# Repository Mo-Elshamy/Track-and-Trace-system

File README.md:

# Track-and-Trace-system 
Used on a medicine production line 
This project is a base module that can be customized for specific purposes.

Youtube link : https://youtu.be/wrTnvzPaxEU

In this project, my role was to establish communication with a microcontroller via a Python app, with the microcontroller responding to any action such as rejection or approval in the production line.

## Python code:

This code is a demonstration of the app code that is responsible for of processing the image from the camera. When the object is detected by the microcontroller, the first section decodes the QR code, and the second section extracts the text from a frame saved as an image.The text from the QR code is then compared to the text from the captured image to make a decision.
The code communicates with the serial library by specifying the port and the baud rate.

## Microconntroller code:

This code is responsible for the app code's actions and also sends a string to the app that acts as a trigger to notify the app code when an object is detected using an IR sensor.

## Hardware circuit:

This circuit is designed to have:
* 4 output relay
* 2 IR sesonrs
* RGBA 12v output connection
* 12v, 5v and GND output
* Input power 24V

## System schematic:

## Pico pinout connection:

## layout design:

## Crcuit:

## Test:

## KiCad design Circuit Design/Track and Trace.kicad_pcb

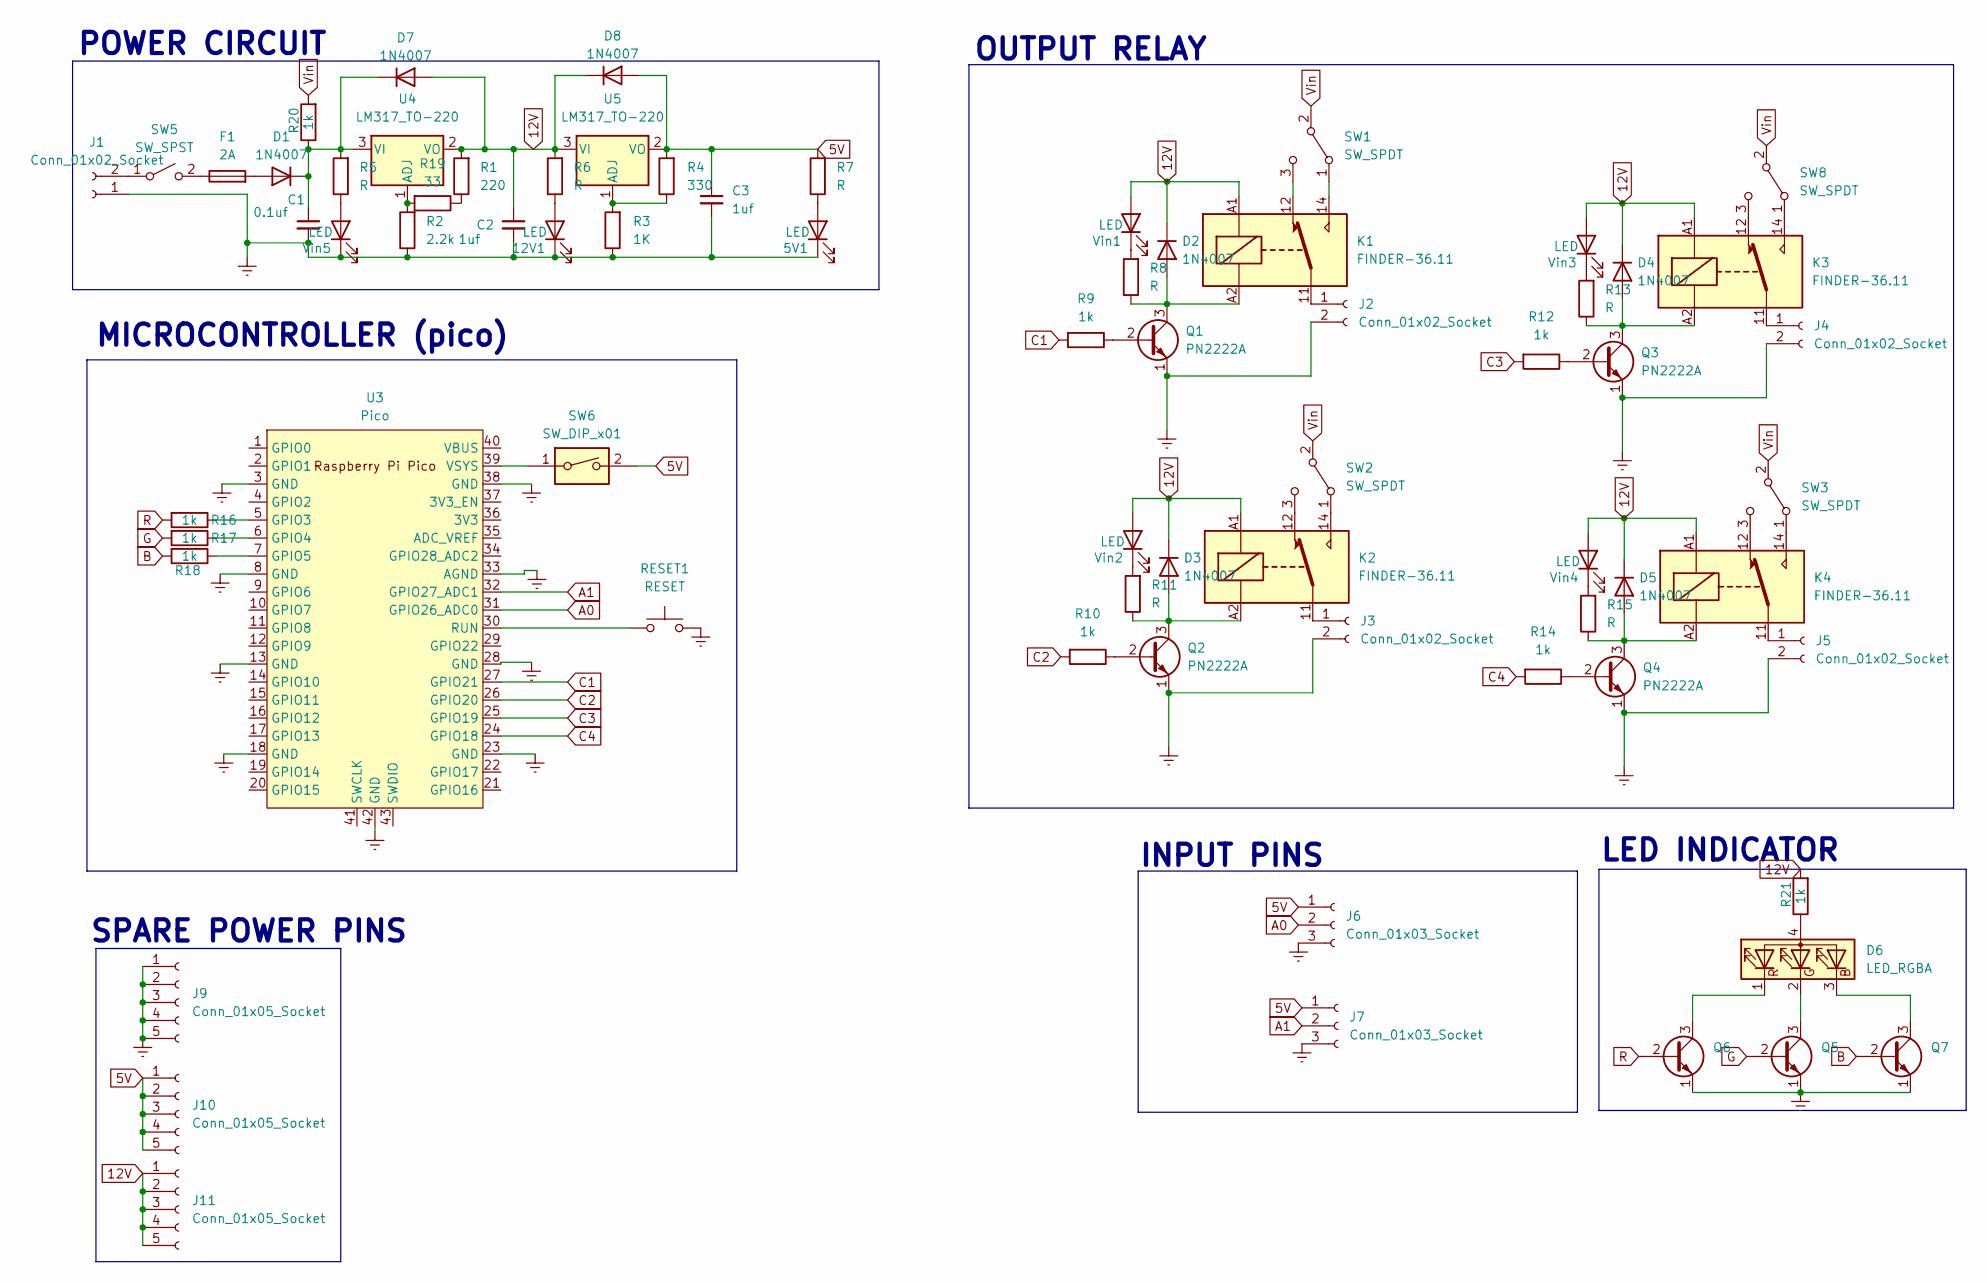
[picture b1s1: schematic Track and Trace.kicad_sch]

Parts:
5V1, 12V1: LED; LED_D3.0mm
C1: 0.1uf; CP_Radial_D4.0mm_P2.00mm
C2, C3: 1uf; CP_Radial_D4.0mm_P2.00mm
D1, D2, D3, D4, D5, D7, D8: 1N4007; D_DO-41_SOD81_P10.16mm_Horizontal
D6: LED_RGBA; JST_EH_B4B-EH-A_1x04_P2.50mm_Vertical
F1: 2A; Fuseholder_Littelfuse_100_series_5x20mm
J1, J2, J3, J4, J5: Conn_01x02_Socket; TerminalBlock_bornier-2_P5.08mm
J6, J7: Conn_01x03_Socket; JST_EH_B3B-EH-A_1x03_P2.50mm_Vertical
J9, J10, J11: Conn_01x05_Socket; TerminalBlock_bornier-5_P5.08mm
K1, K2, K3, K4: FINDER-36.11; Relay_SPDT_Finder_36.11
Q1, Q2, Q3, Q4, Q5, Q6, Q7: PN2222A; TO-92_Inline
R1: 220; R_Axial_DIN0207_L6.3mm_D2.5mm_P10.16mm_Horizontal
R2: 2.2k; R_Axial_DIN0207_L6.3mm_D2.5mm_P10.16mm_Horizontal
R3: 1K; R_Axial_DIN0207_L6.3mm_D2.5mm_P10.16mm_Horizontal
R4: 330; R_Axial_DIN0207_L6.3mm_D2.5mm_P10.16mm_Horizontal
R5, R6, R7, R8, R11, R13, R15: R; R_Axial_DIN0207_L6.3mm_D2.5mm_P10.16mm_Horizontal
R9, R10, R12, R14, R16, R17, R18, R20, R21: 1k; R_Axial_DIN0207_L6.3mm_D2.5mm_P10.16mm_Horizontal
R19: 33; R_Axial_DIN0207_L6.3mm_D2.5mm_P10.16mm_Horizontal
RESET1: RESET; SW_PUSH_6mm_H5mm
SW1, SW2, SW3, SW8: SW_SPDT; PinHeader_1x03_P2.54mm_Vertical
SW5: SW_SPST; TerminalBlock_bornier-2_P5.08mm
SW6: SW_DIP_x01; SW_DIP_SPSTx01_Piano_10.8x4.1mm_W7.62mm_P2.54mm
U3: Pico; RPi_Pico_SMD_TH
U4, U5: LM317_TO-220; TO-220-3_Vertical
Vin1, Vin2, Vin3, Vin4, Vin5: LED; LED_D3.0mm

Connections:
5V: C3.1, D8.2 (A), J6.1, J7.1, J10.1, J10.2, J10.3, J10.4, J10.5, R4.2, R7.2, SW6.2, U5.2 (VO)
12V: C2.1, D2.1 (K), D3.1 (K), D4.1 (K), D5.1 (K), D7.2 (A), D8.1 (K), J11.1, J11.2, J11.3, J11.4, J11.5, K1.A1, K2.A1, K3.A1, K4.A1, R1.2, R6.2, R21.2, U4.2 (VO), U5.3 (VI), Vin1.2 (A), Vin2.2 (A), Vin3.2 (A), Vin4.2 (A)
A0: J6.2, U3.31 (GPIO26_ADC0)
A1: J7.2, U3.32 (GPIO27_ADC1)
B: Q7.2 (B), R18.2
C1: R9.2, U3.27 (GPIO21)
C2: R10.2, U3.26 (GPIO20)
C3: R12.2, U3.25 (GPIO19)
C4: R14.2, U3.24 (GPIO18)
Earth: 5V1.1 (K), 12V1.1 (K), C1.2, C2.2, C3.2, J1.1, J2.2, J3.2, J4.2, J5.2, J6.3, J7.3, J9.1, J9.2, J9.3, J9.4, J9.5, Q1.1 (E), Q2.1 (E), Q3.1 (E), Q4.1 (E), Q5.1 (E), Q6.1 (E), Q7.1 (E), R2.1, R3.1, RESET1.2, U3.3 (GND), U3.8 (GND), U3.13 (GND), U3.18 (GND), U3.23 (GND), U3.28 (GND), U3.33 (AGND), U3.38 (GND), U3.42 (GND), Vin5.1 (K)
G: Q5.2 (B), R17.2
unnamed: 5V1.2 (A), R7.1
unnamed: 12V1.2 (A), R6.1
unnamed: D1.2 (A), F1.2
unnamed: C1.1, D1.1 (K), D7.1 (K), R5.2, R20.1, U4.3 (VI)
unnamed: D2.2 (A), K1.A2, Q1.3 (C), R8.1
unnamed: D3.2 (A), K2.A2, Q2.3 (C), R11.1
unnamed: D4.2 (A), K3.A2, Q3.3 (C), R13.1
unnamed: D5.2 (A), K4.A2, Q4.3 (C), R15.1
unnamed: D6.4 (A), R21.1
unnamed: D6.3 (BK), Q7.3 (C)
unnamed: D6.2 (GK), Q5.3 (C)
unnamed: D6.1 (RK), Q6.3 (C)
unnamed: J1.2, SW5.1 (A)
unnamed: J2.1, K1.11
unnamed: J3.1, K2.11
unnamed: J4.1, K3.11
unnamed: J5.1, K4.11
unnamed: Q1.2 (B), R9.1
unnamed: Q2.2 (B), R10.1
unnamed: Q3.2 (B), R12.1
unnamed: Q4.2 (B), R14.1
unnamed: R1.1, R19.1
unnamed: K1.14, SW1.1 (A)
unnamed: K1.12, SW1.3 (C)
unnamed: K2.14, SW2.1 (A)
unnamed: K2.12, SW2.3 (C)
unnamed: K4.14, SW3.1 (A)
unnamed: K4.12, SW3.3 (C)
unnamed: F1.1, SW5.2 (B)
unnamed: K3.14, SW8.1 (A)
unnamed: K3.12, SW8.3 (C)
unnamed: R16.1, U3.5 (GPIO3)
unnamed: R17.1, U3.6 (GPIO4)
unnamed: R18.1, U3.7 (GPIO5)
unnamed: RESET1.1, U3.30 (RUN)
unnamed: SW6.1, U3.39 (VSYS)
unnamed: R2.2, R19.2, U4.1 (ADJ)
unnamed: R3.2, R4.1, U5.1 (ADJ)
unnamed: R8.2, Vin1.1 (K)
unnamed: R11.2, Vin2.1 (K)
unnamed: R13.2, Vin3.1 (K)
unnamed: R15.2, Vin4.1 (K)
unnamed: R5.1, Vin5.2 (A)
R: Q6.2 (B), R16.2
Vin: R20.2, SW1.2 (B), SW2.2 (B), SW3.2 (B), SW8.2 (B)

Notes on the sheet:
SPARE POWER PINS
LED INDICATOR
MICROCONTROLLER (pico)
OUTPUT RELAY
INPUT PINS
POWER CIRCUIT

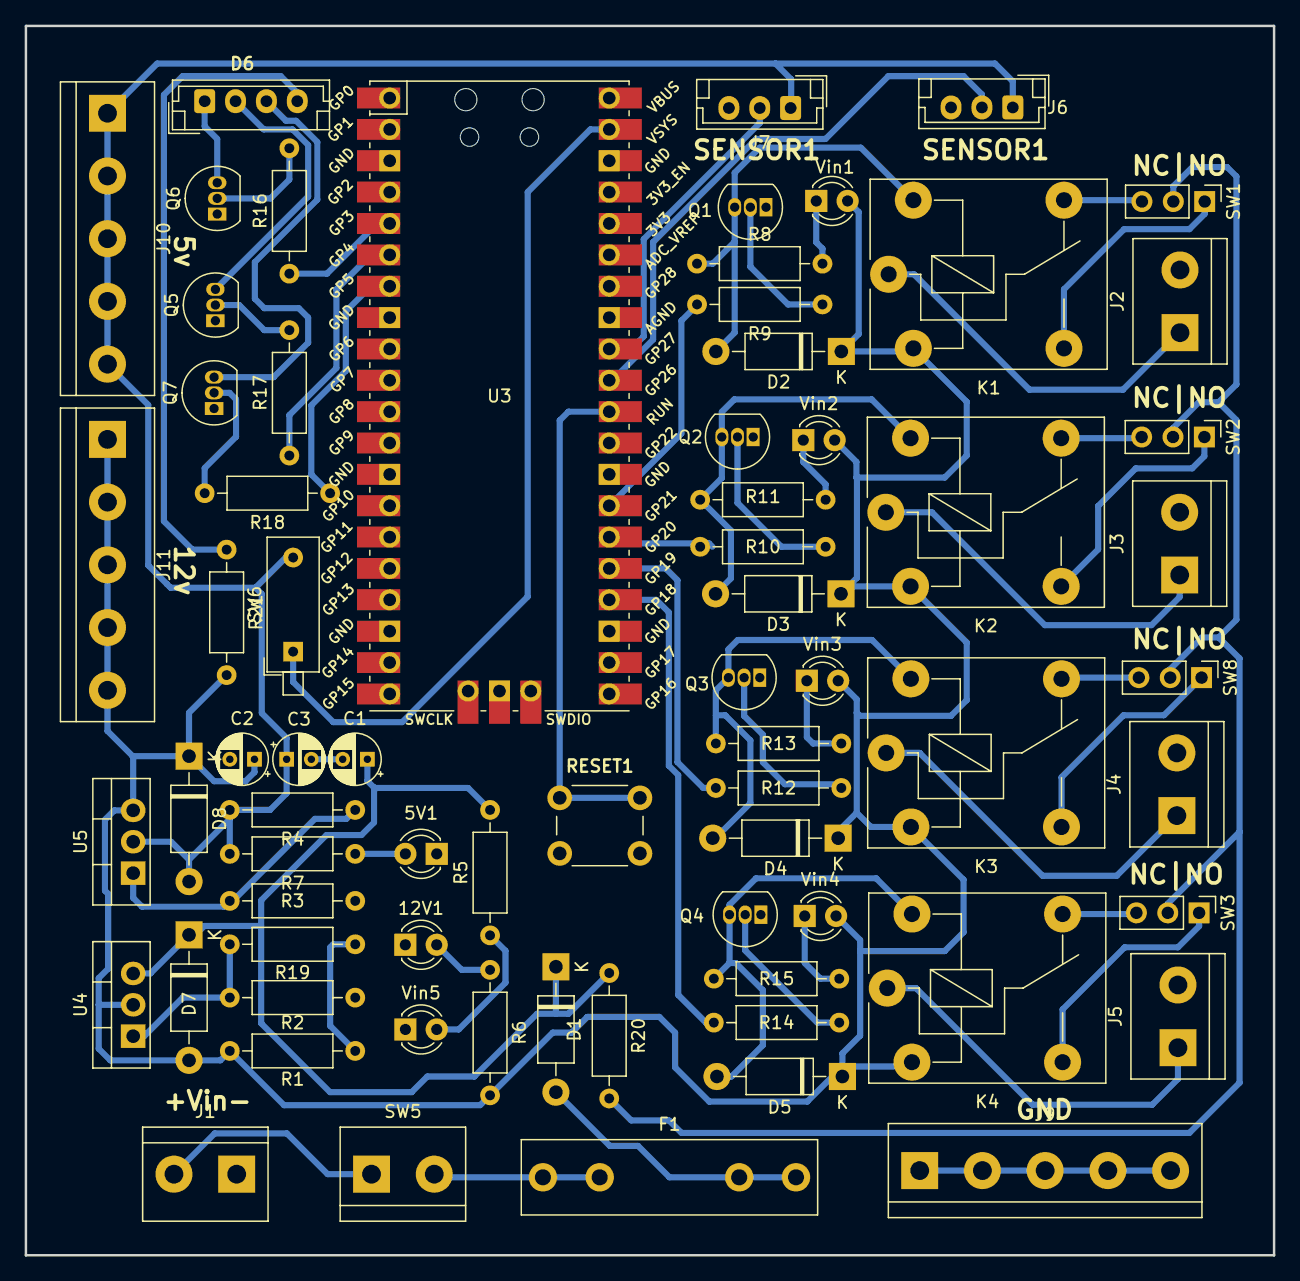
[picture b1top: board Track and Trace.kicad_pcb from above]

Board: 2 copper layers, 101.1 x 99.6 mm, 71 parts (0 on the bottom side), 56 nets.

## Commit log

2023-10-30 Initiating the repo
